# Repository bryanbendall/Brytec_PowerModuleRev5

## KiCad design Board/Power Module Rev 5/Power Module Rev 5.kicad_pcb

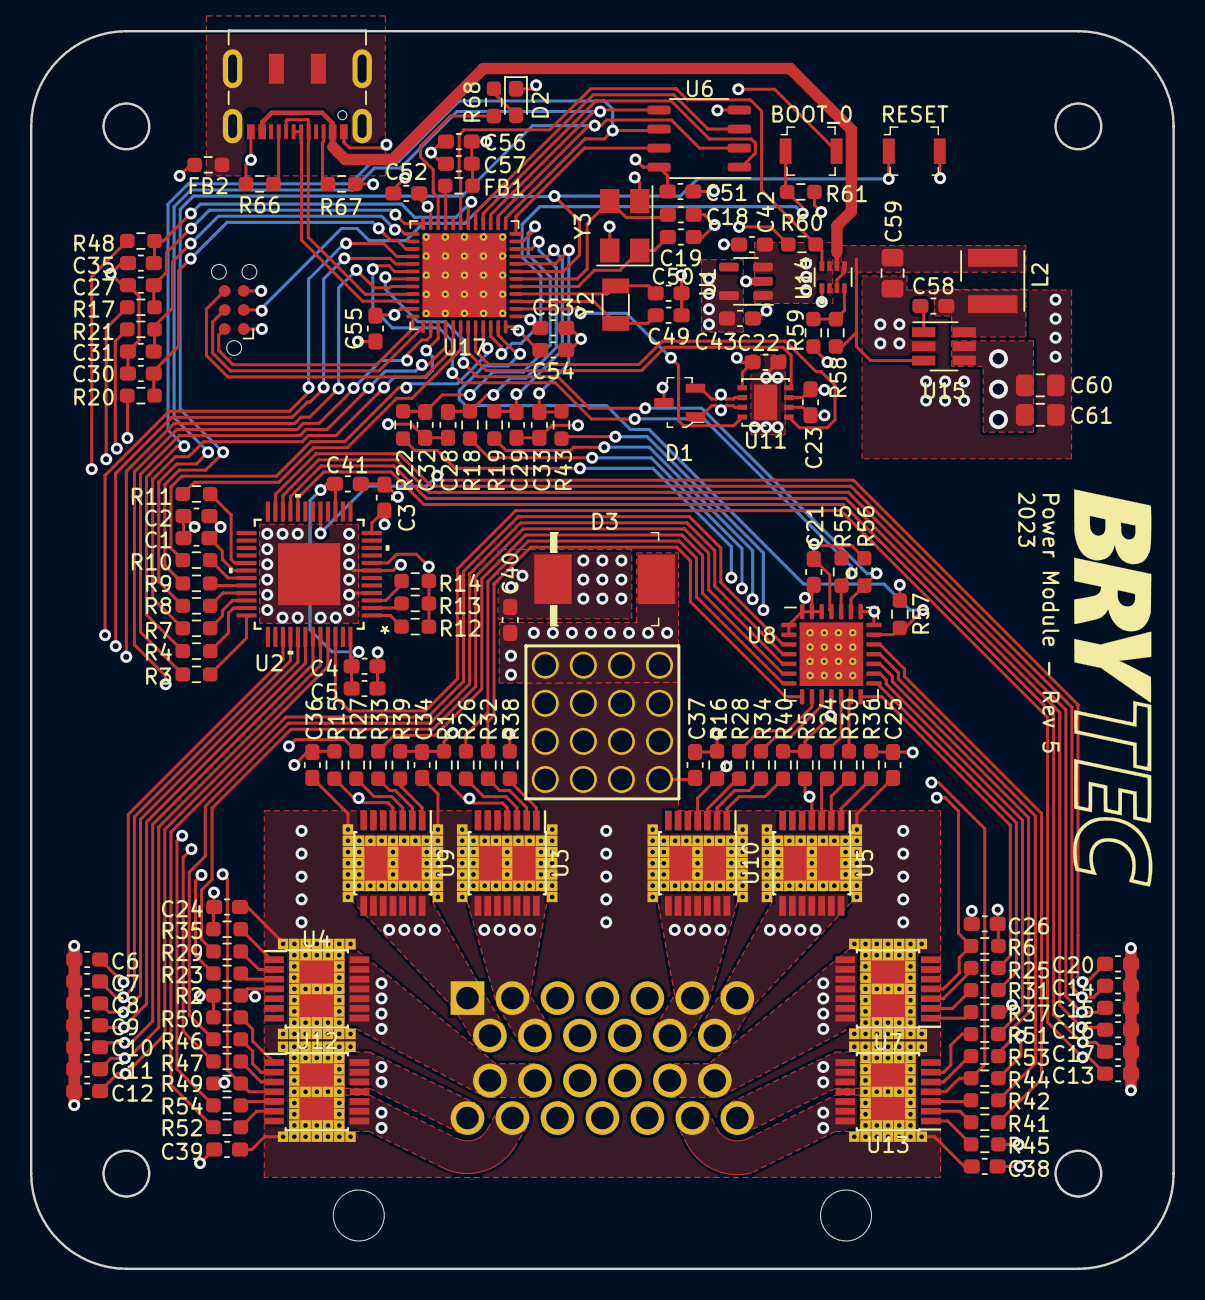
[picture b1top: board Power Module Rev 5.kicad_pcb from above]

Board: 4 copper layers, 76.2 x 82.6 mm, 150 parts (0 on the bottom side), 133 nets.

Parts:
C1, C4, C42, C43, C56: 1uF; C_0603_1608Metric_Pad1.08x0.95mm_HandSolder
C2, C3, C5, C21, C22, C23, C24, C25, C26, C34, C36, C37, C38, C39, C40, C41, C51, C52, C53, C54, C55, C58: 0.1uF; C_0603_1608Metric_Pad1.08x0.95mm_HandSolder
C6, C7, C8, C9, C10, C11, C12, C13, C14, C15, C16, C17, C20: 6.8nF; C_0603_1608Metric_Pad1.08x0.95mm_HandSolder
C18, C19, C49, C50: 10pF; C_0603_1608Metric_Pad1.08x0.95mm_HandSolder
C27, C28, C29, C30, C31, C32, C33, C35: 220pF; C_0603_1608Metric_Pad1.08x0.95mm_HandSolder
C57: 10nF; C_0603_1608Metric_Pad1.08x0.95mm_HandSolder
C59: 10uF; C_0805_2012Metric_Pad1.18x1.45mm_HandSolder
C60: 0.1uF; C_0805_2012Metric_Pad1.18x1.45mm_HandSolder
C61: 4.7uF; C_0805_2012Metric_Pad1.18x1.45mm_HandSolder
D1: PESD2CAN_215; SOT-23-3
D2: LED_Small; LED_0603_1608Metric_Pad1.05x0.95mm_HandSolder
D3: SMCJ33CA; DO-214AB
FB1, FB2: FerriteBead_Small; R_0603_1608Metric_Pad0.98x0.95mm_HandSolder
J1: 9-6437287-8; TE_9-6437287-8
J2: Conn_ARM_SWD_TagConnect_TC2030-NL; Tag-Connect_TC2030-IDC-NL_2x03_P1.27mm_Vertical
J3: Conn_01x16_Pin; WP-BUFU_7461097_HAL
J4: USB_C_Receptacle_USB2.0; USB_C_Receptacle_JAE_DX07S016JA1R1500
L2: 6.8uH; L_Wurth_WE-LQSH-4020
R1, R2, R5, R6, R15, R16, R44, R49: 1.2K; R_0603_1608Metric_Pad0.98x0.95mm_HandSolder
R3, R4, R7, R8, R9, R10, R11: 1K; R_0603_1608Metric_Pad0.98x0.95mm_HandSolder
R12: 50K; R_0603_1608Metric_Pad0.98x0.95mm_HandSolder
R13: 9K; R_0603_1608Metric_Pad0.98x0.95mm_HandSolder
R14: 180; R_0603_1608Metric_Pad0.98x0.95mm_HandSolder
R17, R18, R19, R20, R21, R22, R23, R24, R25, R26, R27, R28, R29, R30, R31, R32, R33, R34, R41, R42, R43, R46, R47, R48, R51, R52, R53, R54, R55, R56: 4.7K; R_0603_1608Metric_Pad0.98x0.95mm_HandSolder
R35, R36, R37, R38, R39, R40, R45, R50: 47; R_0603_1608Metric_Pad0.98x0.95mm_HandSolder
R57, R58, R59, R60, R61: 10K; R_0603_1608Metric_Pad0.98x0.95mm_HandSolder
R66, R67: 5.1K; R_0603_1608Metric_Pad0.98x0.95mm_HandSolder
R68: 65; R_0603_1608Metric_Pad0.98x0.95mm_HandSolder
S1, S2: B3U-1000P; Switch_Tactile_SMD_B3U-1000P
U1: AP2112K-3.3; SOT-23-5
U2: L9966CB-TR; TQFP48_L9966_STM
U3, U4, U5, U7, U9, U10: BTS7002-1EPP; Infineon_PG-TSDSO-14-22 - thermal vias
U6: MB85RS64; SSOP-8_3.9x5.05mm_P1.27mm
U8: PCA9685BS; QFN-28-1EP_6x6mm_P0.65mm_EP4.25x4.25mm_ThermalVias
U11: MCP2558FD-xMF; DFN-8-1EP_3x3mm_P0.65mm_EP1.55x2.4mm
U12, U13: BTS7008-2EPA; Infineon_PG-TSDSO-14-22 - thermal vias
U14: TPS2116DRLR; SOTFL50P160X60-8N
U15: LMR50410Y5FQDBVRQ1; SOT-23-6_Handsoldering
U17: STM32G491CEUx; QFN-48-1EP_7x7mm_P0.5mm_EP5.6x5.6mm_ThermalVias
Y2: 32.768kHz; Crystal_SMD_3215-2Pin_3.2x1.5mm
Y3: 8MHz; Crystal_SMD_5032-4Pin_5.0x3.2mm

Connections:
+3.3V: C22.1, C43.1, C51.1, C52.2, C53.2, C54.2, C55.2, C56.2, C57.2, FB1.1, J2.1 (VCC), R60.1, S2.2, U1.5 (VOUT), U6.8 (VDD), U11.5 (VIO), U17.1 (VBAT), U17.23 (VDD), U17.35 (VDD), U17.48 (VDD)
+5V: C1.1, C2.1, C3.2, C21.1, C23.1, C42.1, J1.11, R12.1, R13.1, R14.1, R55.1, R56.1, R57.1, U1.1 (VIN), U1.3 (EN), U2.8 (VDD5REF), U2.12 (VI5V), U2.30 (VDD5V), U8.25 (VDD), U11.3 (VDD), U14.2 (VOUT), U14.7 (VOUT)
+12V: C4.1, C5.1, C24.1, C25.1, C26.1, C34.1, C36.1, C37.1, C38.1, C39.1, C40.1, C41.2, D3.2 (A2), J3.1, J3.2, J3.3, J3.4, J3.5, J3.6, J3.7, J3.8, J3.9, J3.10, J3.11, J3.12, J3.13, J3.14, J3.15, J3.16, U2.15 (VIX), U2.48 (UBSW), U3.15 (VS), U4.15 (VS), U5.15 (VS), U7.15 (VS), U9.15 (VS), U10.15 (VS), U12.15 (VS), U13.15 (VS)
/High Side Drivers/Den1: R26.2, U8.7 (LED4)
/High Side Drivers/Den3: R24.2, U8.12 (LED8)
/High Side Drivers/Den4: R25.2, U8.14 (LED10)
/High Side Drivers/Den6: R28.2, U8.9 (LED6)
/High Side Drivers/Den9-10: R42.2, U8.18 (LED14)
/High Side Drivers/Dsel9-10: R53.2, U8.17 (LED13)
/High Side Drivers/In1: R32.2, U8.8 (LED5)
/High Side Drivers/In2: R29.2, U8.5 (LED2)
/High Side Drivers/In3: R30.2, U8.13 (LED9)
/High Side Drivers/In4: R31.2, U8.15 (LED11)
/High Side Drivers/In5: R33.2, U8.6 (LED3)
/High Side Drivers/In6: R34.2, U8.10 (LED7)
/High Side Drivers/In7: R46.2, U8.4 (LED1)
/High Side Drivers/In8: R52.2, U8.3 (LED0)
/High Side Drivers/In9: R41.2, U8.19 (LED15)
/High Side Drivers/In10: R51.2, U8.16 (LED12)
/Mcu/BOOT_0: R61.1, S2.1, U17.46 (PB8)
/Mcu/Memory_Hold: U6.7 (~HOLD), U17.12 (PA4)
/Mcu/Memory_Wp: U6.3 (~WP), U17.17 (PB0)
/Mcu/RESET: J2.3 (~RESET), S1.1, U17.7 (PG10)
/Mcu/SPI1_SS_Memory: U6.1 (~CS), U17.16 (PC4)
/Mcu/SWCLK: J2.4 (SWCLK), U17.37 (PA14)
/Mcu/SWDIO: J2.2 (SWDIO), U17.36 (PA13)
/Mcu/SWO: J2.6 (SWO), U17.41 (PB3)
/Mcu/Usb D+: J4.A6 (D+), J4.B6 (D+), U17.34 (PA12)
/Mcu/Usb D-: J4.A7 (D-), J4.B7 (D-), U17.33 (PA11)
/Mcu/Usb_Shield: FB2.1, J4.S1 (SHIELD)
/Mcu/User_Led: R68.1, U17.22 (PB10)
Can+: D1.1 (C1), J1.4, U11.7 (CANH)
Can-: D1.2 (C2), J1.3, U11.6 (CANL)
CanRx: U11.4 (RXD), U17.43 (PB5)
CanSilent: U11.8 (S), U17.2 (PC13)
CanTx: U11.1 (TXD), U17.44 (PB6)
Den2: R23.2, U17.28 (PB15)
Den5: R27.2, U17.38 (PA15)
Den7-8: R47.2, U17.32 (PA10)
Dsel7-8: R54.2, U17.29 (PC6)
GND: C1.2, C2.2, C3.1, C4.2, C5.2, C6.2, C7.2, C8.2, C9.2, C10.2, C11.2, C12.2, C13.2, C14.2, C15.2, C16.2, C17.2, C18.1, C19.1, C20.2, C21.2, C22.2, C23.2, C24.2, C25.2, C26.2, C27.2, C28.2, C29.2, C30.2, C31.2, C32.2, C33.2, C34.2, C35.2, C36.2, C37.2, C38.2, C39.2, C40.2, C41.1, C42.2, C43.2, C49.1, C50.1, C51.2, C52.1, C53.1, C54.1, C55.1, C56.1, C57.1, C59.2, C60.2, C61.2, D1.3 (C3), D2.1 (K), D3.1 (A1), FB2.2, J1.10, J1.16, J1.17, J2.5 (GND), J4.A1 (GND), J4.A12 (GND), J4.B1 (GND), J4.B12 (GND), R1.2, R2.2, R5.2, R6.2, R15.2, R16.2, R35.2, R36.2, R37.2, R38.2, R39.2, R40.2, R44.2, R45.2, R49.2, R50.2, R59.2, R61.2, R66.2, R67.2, S1.2, U1.2 (GND), U2.4 (R_GND), U2.7 (GND), U2.EPAD, U6.4 (GND), U8.1 (A3), U8.2 (A4), U8.11 (VSS), U8.21 (A5), U8.22 (EXTCLK), U8.26 (A0), U8.27 (A1), U8.28 (A2), U8.29 (VSS), U11.2 (VSS), U11.9 (VSS), U14.1 (GND), U15.2 (GND), U17.49 (VSS), Y3.2, Y3.4
Ignition: C60.1, C61.1, J1.5, U15.4 (EN), U15.5 (VIN)
Input1: C13.1, J1.24, U2.46 (IO_5)
Input2: C12.1, J1.23, U2.45 (IO_6)
Input3: C11.1, J1.22, U2.44 (IO_7)
Is1: C30.1, R20.2, U17.27 (PB14)
Is2: C27.1, R17.2, U17.24 (PB11)
Is3: C28.1, R18.2, U17.10 (PA2)
Is4: C29.1, R19.2, U17.9 (PA1)
Is5: C31.1, R21.2, U17.25 (PB12)
Is6: C32.1, R22.2, U17.11 (PA3)
Is7-8: C35.1, R48.2, U17.18 (PB1)
Is9-10: C33.1, R43.2, U17.8 (PA0)
L6699-Int: R11.2, U17.42 (PB4)
L6699-Rst: R3.2, U17.40 (PC11)
L6699-Sync: R10.2, U17.45 (PB7)
unnamed: D2.2 (A), R68.2
unnamed: J4.A5 (CC1), R67.1
unnamed: J4.B5 (CC2), R66.1
unnamed: R7.1, U2.34 (CS)
unnamed: R11.1, U2.29 (INT)
unnamed: R9.1, U2.32 (MISO)
unnamed: R8.1, U2.33 (MOSI)
unnamed: R14.2, U2.3 (RR1)
unnamed: R13.2, U2.2 (RR2)
unnamed: R12.2, U2.1 (RR3)
unnamed: R3.1, U2.36 (RST)
unnamed: R4.1, U2.35 (SCLK)
unnamed: R10.1, U2.31 (SYNC)
unnamed: R26.1, U3.3 (DEN)
unnamed: R38.1, U3.1 (GND)
unnamed: R32.1, U3.2 (IN)
unnamed: R1.1, R20.1, U3.4 (IS)
unnamed: R23.1, U4.3 (DEN)
unnamed: R35.1, U4.1 (GND)
unnamed: R29.1, U4.2 (IN)
unnamed: R2.1, R17.1, U4.4 (IS)
unnamed: R24.1, U5.3 (DEN)
unnamed: R36.1, U5.1 (GND)
unnamed: R30.1, U5.2 (IN)
unnamed: R5.1, R18.1, U5.4 (IS)
unnamed: R25.1, U7.3 (DEN)
unnamed: R37.1, U7.1 (GND)
unnamed: R31.1, U7.2 (IN)
unnamed: R6.1, R19.1, U7.4 (IS)
unnamed: R27.1, U9.3 (DEN)
unnamed: R39.1, U9.1 (GND)
unnamed: R33.1, U9.2 (IN)
unnamed: R15.1, R21.1, U9.4 (IS)
unnamed: R28.1, U10.3 (DEN)
unnamed: R40.1, U10.1 (GND)
unnamed: R34.1, U10.2 (IN)
unnamed: R16.1, R22.1, U10.4 (IS)
unnamed: R47.1, U12.3 (DEN)
unnamed: R54.1, U12.5 (DSEL)
unnamed: R50.1, U12.1 (GND)
unnamed: R46.1, U12.2 (IN0)
unnamed: R52.1, U12.6 (IN1)
unnamed: R48.1, R49.1, U12.4 (IS)
unnamed: R42.1, U13.3 (DEN)
unnamed: R53.1, U13.5 (DSEL)
unnamed: R45.1, U13.1 (GND)
unnamed: R41.1, U13.2 (IN0)
unnamed: R51.1, U13.6 (IN1)
unnamed: R43.1, R44.1, U13.4 (IS)
unnamed: R58.2, R59.1, U14.4 (PR1)
unnamed: C58.2, U15.1 (CB)
unnamed: C58.1, L2.1, U15.6 (SW)
unnamed: C49.2, U17.3 (PC14), Y2.2
unnamed: C50.2, U17.4 (PC15), Y2.1
unnamed: C19.2, U17.5 (PF0), Y3.1
unnamed: C18.2, U17.6 (PF1), Y3.3
unnamed: FB1.2, U17.21 (VDDA)
Output1: C7.1, J1.2, J1.9, U2.40 (IO_11), U3.8 (OUT), U3.9 (OUT), U3.10 (OUT), U3.11 (OUT), U3.12 (OUT), U3.13 (OUT), U3.14 (OUT)
Output2: C8.1, J1.14, J1.15, U2.41 (IO_10), U4.8 (OUT), U4.9 (OUT), U4.10 (OUT), U4.11 (OUT), U4.12 (OUT), U4.13 (OUT), U4.14 (OUT)
Output3: C20.1, J1.7, J1.13, U2.17 (IO_13), U5.8 (OUT), U5.9 (OUT), U5.10 (OUT), U5.11 (OUT), U5.12 (OUT), U5.13 (OUT), U5.14 (OUT)
Output4: C15.1, J1.18, J1.19, U2.22 (IO_3), U7.8 (OUT), U7.9 (OUT), U7.10 (OUT), U7.11 (OUT), U7.12 (OUT), U7.13 (OUT), U7.14 (OUT)
Output5: C6.1, J1.1, J1.8, U2.39 (IO_12), U9.8 (OUT), U9.9 (OUT), U9.10 (OUT), U9.11 (OUT), U9.12 (OUT), U9.13 (OUT), U9.14 (OUT)
Output6: C14.1, J1.6, J1.12, U2.23 (IO_4), U10.8 (OUT), U10.9 (OUT), U10.10 (OUT), U10.11 (OUT), U10.12 (OUT), U10.13 (OUT), U10.14 (OUT)
Output7: C9.1, J1.20, U2.42 (IO_9), U12.12 (OUT0), U12.13 (OUT0), U12.14 (OUT0)
Output8: C10.1, J1.21, U2.43 (IO_8), U12.8 (OUT1), U12.9 (OUT1), U12.10 (OUT1)
Output9: C17.1, J1.25, U2.20 (IO_1), U13.12 (OUT0), U13.13 (OUT0), U13.14 (OUT0)
Output10: C16.1, J1.26, U2.21 (IO_2), U13.8 (OUT1), U13.9 (OUT1), U13.10 (OUT1)
PowerSwitchStatus: R60.2, U14.8 (ST), U17.19 (PB2)
Pwm_Ctr_Enable: R57.2, U8.20 (~OE), U17.47 (PB9)
Regulated 5V: C59.1, L2.2, R58.1, U14.3 (VIN1), U14.5 (MODE), U15.3 (FB)
SCL: R56.2, U8.23 (SCL), U17.31 (PA9)
SDA: R55.2, U8.24 (SDA), U17.30 (PA8)
SPI1_Miso: R9.2, U6.2 (SO), U17.14 (PA6)
SPI1_Mosi: R8.2, U6.5 (SI), U17.15 (PA7)
SPI1_SS_L9966: R7.2, U17.39 (PC10)
SPI1_Sclk: R4.2, U6.6 (SCK), U17.13 (PA5)
Usb 5V: J4.A4 (VBUS), J4.A9 (VBUS), J4.B4 (VBUS), J4.B9 (VBUS), U14.6 (VIN2)

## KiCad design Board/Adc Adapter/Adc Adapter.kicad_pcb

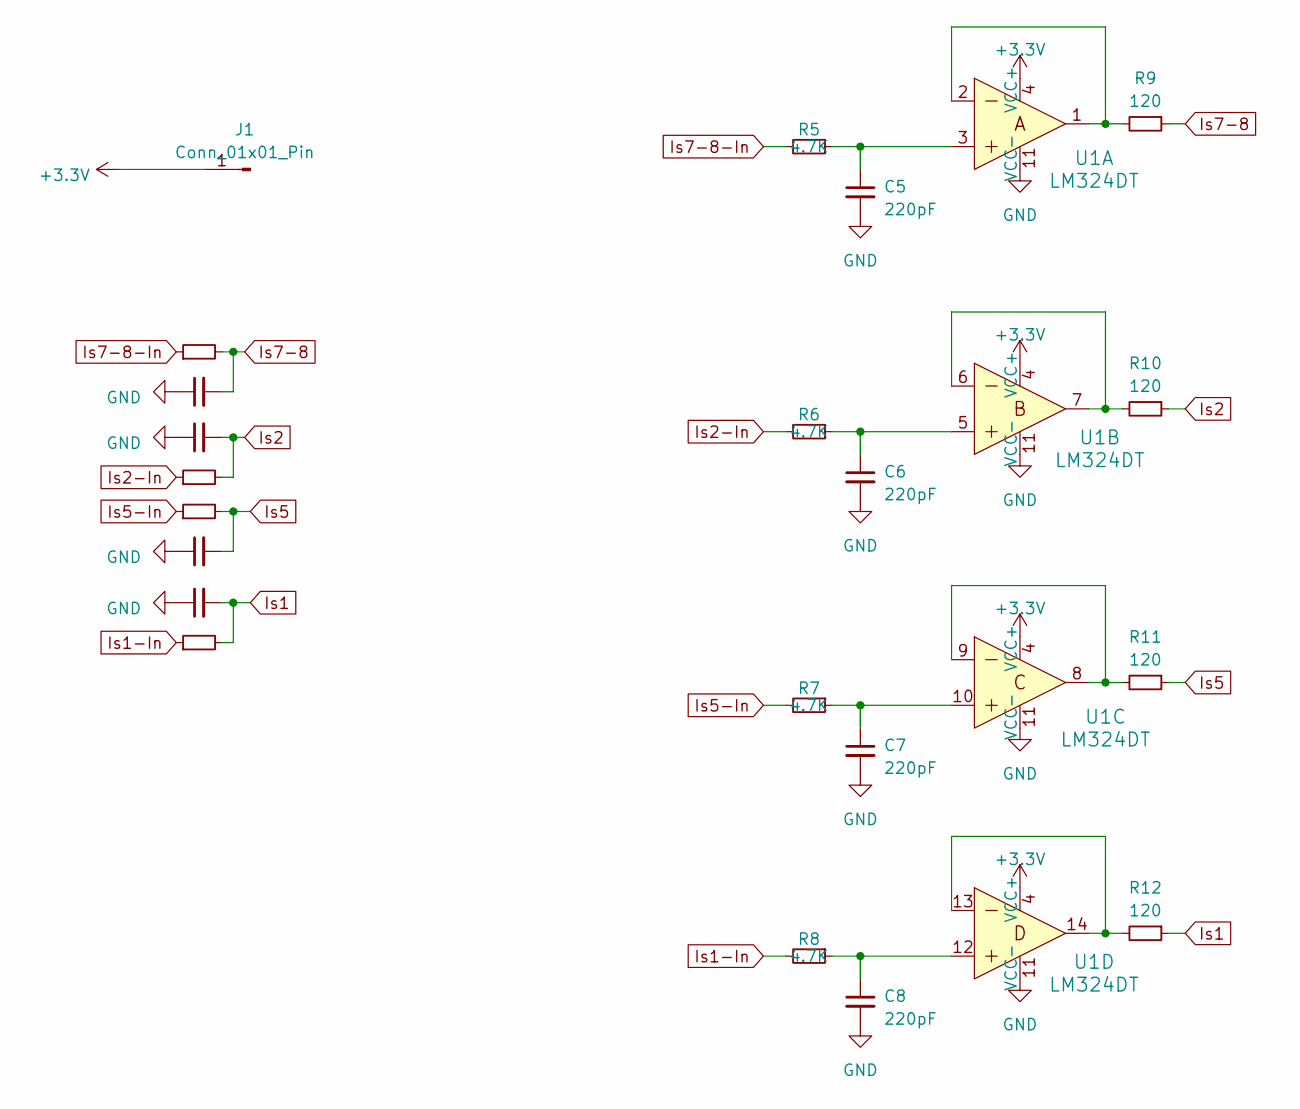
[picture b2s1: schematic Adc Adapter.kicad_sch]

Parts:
C1, C2, C3, C4: C_Small; C_0603_1608Metric_Adaptor
C5, C6, C7, C8: 220pF; C_0603_1608Metric_Pad1.08x0.95mm_HandSolder
J1: Conn_01x01_Pin; PinHeader_1x01_P2.00mm_Vertical
R1, R2, R3, R4: R_Small; C_0603_1608Metric_Adaptor
R5, R6, R7, R8: 4.7K; R_0603_1608Metric_Pad0.98x0.95mm_HandSolder
R9, R10, R11, R12: 120; R_0603_1608Metric_Pad0.98x0.95mm_HandSolder
U1: LM324DT; SOIC-14_W3.9mm; MPN LM324DT; Digi-Key_PN 497-1580-1-ND

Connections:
+3.3V: J1.1, U1.4 (VCC+)
GND: C1.1, C2.1, C3.1, C4.1, C5.2, C6.2, C7.2, C8.2, U1.11 (VCC-)
Is1: C4.2, R4.2, R12.1
Is1-In: R4.1, R8.2
Is2: C2.2, R2.2, R10.1
Is2-In: R2.1, R6.2
Is5: C3.2, R3.2, R11.1
Is5-In: R3.1, R7.2
Is7-8: C1.2, R1.2, R9.1
Is7-8-In: R1.1, R5.2
unnamed: C5.1, R5.1, U1.3
unnamed: C6.1, R6.1, U1.5
unnamed: C7.1, R7.1, U1.10
unnamed: C8.1, R8.1, U1.12
unnamed: R9.2, U1.1, U1.2
unnamed: R10.2, U1.6, U1.7
unnamed: R11.2, U1.8, U1.9
unnamed: R12.2, U1.13, U1.14

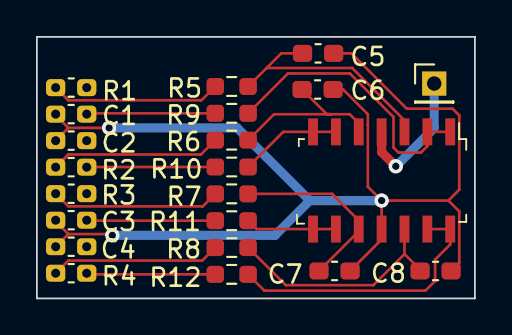
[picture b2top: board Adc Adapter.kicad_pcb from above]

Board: 2 copper layers, 24.3 x 14.5 mm, 22 parts (0 on the bottom side), 18 nets.

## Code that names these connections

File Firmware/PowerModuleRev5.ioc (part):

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Mcu.Name=STM32G491C(C-E)Ux
Mcu.Package=UFQFPN48
Mcu.UserName=STM32G491CEUx
PA0.GPIOParameters=GPIO_PuPd,GPIO_Label,GPIO_Mode
PA0.GPIO_Label=Is9-10
PA0.GPIO_Mode=GPIO_MODE_ANALOG
PA0.GPIO_PuPd=GPIO_NOPULL
PA0.Mode=IN1-Single-Ended
PA0.Signal=ADC1_IN1
PA1.GPIOParameters=GPIO_PuPd,GPIO_Label,GPIO_Mode
PA1.GPIO_Label=Is4
PA1.GPIO_Mode=GPIO_MODE_ANALOG
PA1.GPIO_PuPd=GPIO_NOPULL
PA1.Mode=IN2-Single-Ended
PA1.Signal=ADC1_IN2
PA10.GPIOParameters=GPIO_Label
PA10.GPIO_Label=Den7-8
PA10.Signal=GPIO_Output
PA11.Mode=Device
PA11.Signal=USB_DM
PA12.Mode=Device
PA12.Signal=USB_DP
PA13.Mode=Serial_Wire
PA13.Signal=SYS_JTMS-SWDIO
PA14.Mode=Serial_Wire
PA14.Signal=SYS_JTCK-SWCLK
PA15.GPIOParameters=GPIO_Label
PA15.GPIO_Label=Den5
PA15.Signal=GPIO_Output
PA2.GPIOParameters=GPIO_PuPd,GPIO_Label,GPIO_Mode
PA2.GPIO_Label=Is3
PA2.GPIO_Mode=GPIO_MODE_ANALOG
PA2.GPIO_PuPd=GPIO_NOPULL
PA2.Mode=IN3-Single-Ended
PA2.Signal=ADC1_IN3
PA3.GPIOParameters=GPIO_PuPd,GPIO_Label,GPIO_Mode
PA3.GPIO_Label=Is6
PA3.GPIO_Mode=GPIO_MODE_ANALOG
PA3.GPIO_PuPd=GPIO_NOPULL
PA3.Mode=IN4-Single-Ended
PA3.Signal=ADC1_IN4
PA4.GPIOParameters=PinState,GPIO_Label
PA4.GPIO_Label=Memory_Hold
PA4.PinState=GPIO_PIN_SET
PA4.Signal=GPIO_Output
PA5.Mode=Full_Duplex_Master
PA5.Signal=SPI1_SCK
PA6.Mode=Full_Duplex_Master
PA6.Signal=SPI1_MISO
PA7.Mode=Full_Duplex_Master
PA7.Signal=SPI1_MOSI
PA8.Mode=I2C
PA8.Signal=I2C2_SDA
PA9.Mode=I2C
PA9.Signal=I2C2_SCL
PB0.GPIOParameters=PinState,GPIO_Label
PB0.GPIO_Label=Memory_Wp
PB0.PinState=GPIO_PIN_SET
PB0.Signal=GPIO_Output
PB1.GPIOParameters=GPIO_PuPd,GPIO_Label,GPIO_Mode
PB1.GPIO_Label=Is7-8
PB1.GPIO_Mode=GPIO_MODE_ANALOG
PB1.GPIO_PuPd=GPIO_NOPULL
PB1.Mode=IN12-Single-Ended
PB1.Signal=ADC1_IN12
PB10.GPIOParameters=GPIO_Label
PB10.GPIO_Label=User_Led
PB10.Signal=GPIO_Output
PB11.GPIOParameters=GPIO_PuPd,GPIO_Label,GPIO_Mode
PB11.GPIO_Label=Is2
PB11.GPIO_Mode=GPIO_MODE_ANALOG
PB11.GPIO_PuPd=GPIO_NOPULL
PB11.Mode=IN14-Single-Ended
PB11.Signal=ADC1_IN14
PB12.GPIOParameters=GPIO_PuPd,GPIO_Label,GPIO_Mode
PB12.GPIO_Label=Is5
PB12.GPIO_Mode=GPIO_MODE_ANALOG
PB12.GPIO_PuPd=GPIO_NOPULL
PB12.Mode=IN11-Single-Ended
PB12.Signal=ADC1_IN11
PB14.GPIOParameters=GPIO_PuPd,GPIO_Label,GPIO_Mode
PB14.GPIO_Label=Is1
PB14.GPIO_Mode=GPIO_MODE_ANALOG
PB14.GPIO_PuPd=GPIO_NOPULL
PB14.Mode=IN5-Single-Ended
PB14.Signal=ADC1_IN5
PB15.GPIOParameters=GPIO_Label
PB15.GPIO_Label=Den2
PB15.Signal=GPIO_Output
PB2.GPIOParameters=GPIO_Label
PB2.GPIO_Label=PowerSwitchStatus
PB2.Signal=GPIO_Input
PB3.Signal=SYS_JTDO-SWO
PB4.GPIOParameters=GPIO_Label
PB4.GPIO_Label=L9966-Int
PB4.Signal=GPIO_Input
PB5.Mode=FDCAN_Activate
PB5.Signal=FDCAN2_RX
PB6.Mode=FDCAN_Activate
PB6.Signal=FDCAN2_TX
PB7.GPIOParameters=GPIO_Label
PB7.GPIO_Label=L9966-Sync
PB7.Signal=GPIO_Output
PB8-BOOT0.GPIOParameters=GPIO_Label
PB8-BOOT0.GPIO_Label=BOOT_0
PB8-BOOT0.Signal=GPIO_Input
PB9.GPIOParameters=GPIO_Label
PB9.GPIO_Label=Pwm_Ctr_Enable
PB9.Signal=GPIO_Output
PC10.GPIOParameters=PinState,GPIO_Label
PC10.GPIO_Label=SPI_SS_L9966
PC10.PinState=GPIO_PIN_SET
PC10.Signal=GPIO_Output
PC11.GPIOParameters=GPIO_Label
PC11.GPIO_Label=L9966-Rst
PC11.Signal=GPIO_Output
PC13.GPIOParameters=GPIO_Label
PC13.GPIO_Label=CanSilent
PC13.Signal=GPIO_Output
PC14-OSC32_IN.Mode=LSE-External-Oscillator
PC14-OSC32_IN.Signal=RCC_OSC32_IN
PC15-OSC32_OUT.Mode=LSE-External-Oscillator
PC15-OSC32_OUT.Signal=RCC_OSC32_OUT
PC4.GPIOParameters=PinState,GPIO_Label
PC4.GPIO_Label=Memory_SS
PC4.PinState=GPIO_PIN_SET
PC4.Signal=GPIO_Output
PC6.GPIOParameters=GPIO_Label
PC6.GPIO_Label=Dsel7-8
PC6.Signal=GPIO_Output
PF0-OSC_IN.Mode=HSE-External-Oscillator
PF0-OSC_IN.Signal=RCC_OSC_IN
PF1-OSC_OUT.Mode=HSE-External-Oscillator
PF1-OSC_OUT.Signal=RCC_OSC_OUT
PG10-NRST.GPIOParameters=GPIO_Label
PG10-NRST.GPIO_Label=NRST
PG10-NRST.Signal=GPIO_Input
RCC.HSE_VALUE=8000000
RCC.SYSCLKFreq_VALUE=144000000
RCC.SYSCLKSource=RCC_SYSCLKSOURCE_PLLCLK
board=custom

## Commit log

2023-07-27 Add git ignore
2023-07-27 Working on board
2023-07-27 Ti power supply pdf
2023-07-30 Board Progress
2023-08-04 Added microcontroller pinout generator
2023-08-04 Update Board
2023-08-09 Board Update
2023-08-14 Update config and renames on schematic
2023-08-19 Board - changed regulator
2023-08-23 Board Update and Gerbers
2023-08-23 Initial Generated Stm32 Code
2023-08-24 Added cpp main
2023-08-25 Added submodule and updates
2023-09-20 Board update and bom page
2023-09-20 Board defs, debug printing
2023-09-20 Moved stm32 files to submodule
2023-09-23 Saving and Loding config to fram chip
2023-09-29 Update for board files and power outputs Added float printf
2023-09-29 Stm32Files Submodule
2023-10-01 Control diagnostic pins Reorganize Start adc Read power switch state
2023-10-06 Working adc
2023-10-10 Slow adc reading Setup dual output chips
2023-10-17 Refactor to board hardware file Reading pin voltage starting
2023-10-17 Added adc adapter board
2023-10-20 Working voltage and resistance
2023-10-22 Reorganize and clean up board file
2023-10-28 Adc adapter gerber outputs
2023-10-28 Reorder for L9966 before loading config Checking ignition power state
2023-11-16 Updates for submodules
2023-11-20 Enable Can interrupt Updates for submodule
2023-11-24 Setup Can speed
2024-01-26 Board - fixed connector pin numbering
2024-01-26 Fixed pin numbering Update can for changes in submodule
2024-01-30 Updates for submodule
2024-01-31 Moved board input and output files to submodule
2024-02-01 Setup can bus
2024-03-09 Refactor for submodule ms timers
2024-07-19 Remove reading pin voltage Updates for submodules
2024-07-19 Added jump to bootloader
2025-08-30 Updated submodules Init l9966 if 12v applied
